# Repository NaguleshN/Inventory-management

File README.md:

# Inventory-management
The Inventory Management System will track and manage components inside iQube. It will include functionalities for managing product details, tracking stock levels, components taken out and returned back.
hello world.

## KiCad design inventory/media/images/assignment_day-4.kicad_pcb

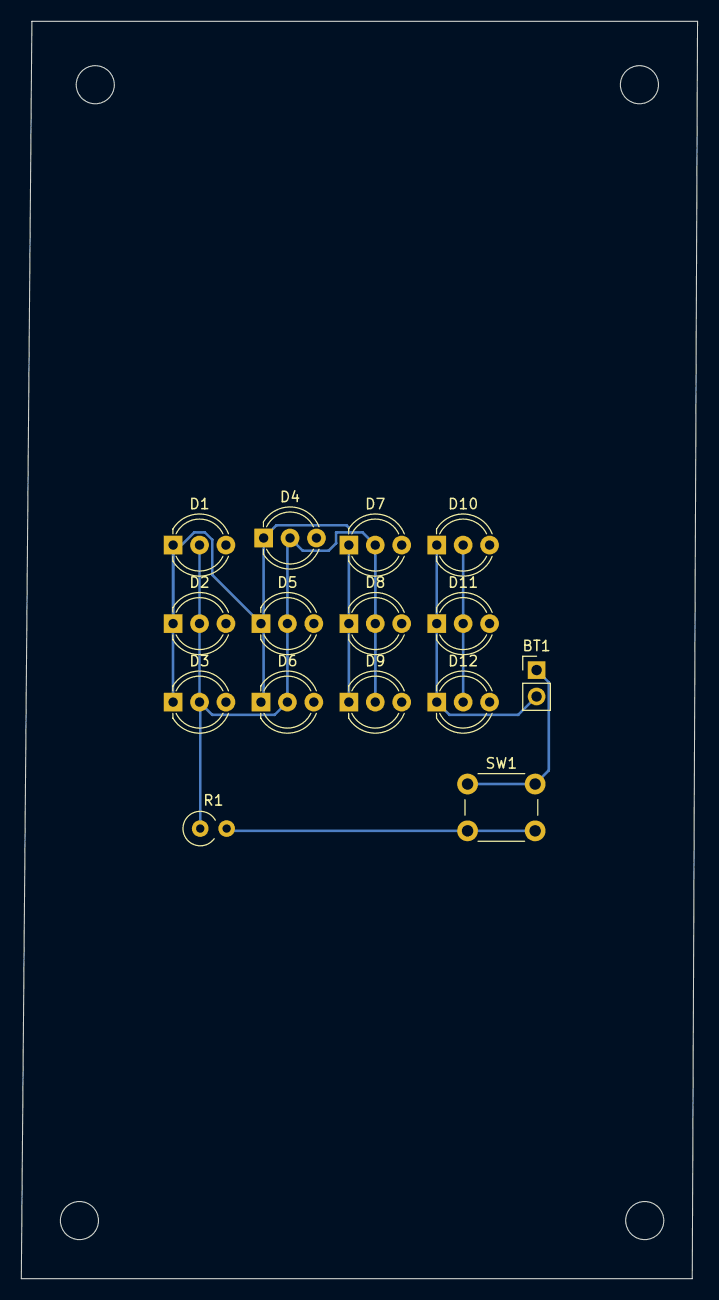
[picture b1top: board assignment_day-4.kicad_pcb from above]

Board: 2 copper layers, 65.0 x 120.9 mm, 15 parts (0 on the bottom side), 4 nets.

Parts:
BT1: Battery; PinHeader_1x02_P2.54mm_Vertical
D1, D2, D3, D4, D5, D6, D7, D8, D9, D10, D11, D12: LED; LED_D5.0mm-3
R1: R; R_Axial_DIN0309_L9.0mm_D3.2mm_P2.54mm_Vertical
SW1: SW_Push; SW_PUSH_6mm

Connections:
unnamed: BT1.1 (+), SW1.1
unnamed: BT1.2 (-), D1.1 (K), D2.1 (K), D3.1 (K), D4.1 (K), D5.1 (K), D6.1 (K), D7.1 (K), D8.1 (K), D9.1 (K), D10.1 (K), D11.1 (K), D12.1 (K)
unnamed: D1.2 (A), D2.2 (A), D3.2 (A), D4.2 (A), D5.2 (A), D6.2 (A), D7.2 (A), D8.2 (A), D9.2 (A), D10.2 (A), D11.2 (A), D12.2 (A), R1.1
unnamed: R1.2, SW1.2

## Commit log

2023-11-18 first change
2023-11-18 gitignore added
2023-11-18 start a project
2023-11-18 db created
2023-11-18 admin created
2023-11-18 db added
2023-11-18 Added foreign key
2023-11-18 category added
2023-11-18 choice added
2023-11-18 db successfully changed
2023-11-18 just Changes
2023-11-18 im chaai
2023-11-18 db delted
2023-11-19 base page added
2023-11-19 base page add
2023-11-19 home views
2023-11-19 Auto stash before merge of "main" and "origin/main"
    added product display
2023-11-19 add_product update
2023-11-19 query change
2023-11-19 about_page added
2023-11-19 Auto stash before merge of "main" and "origin/main"
    category page added
2023-11-19 Auto stash before merge of "main" and "origin/main"
    Wastage page added
2023-11-19 added view for category
2023-11-19 new feature
2023-11-19 Auto stash before merge of "main" and "origin/main"
    Wastage_page added with functionality
2023-11-19 gitignore
2023-11-19 pacth update
2023-11-19 added product description and cart btn
2023-11-19 added changes in cards and cart
2023-11-19 cart added
2023-11-19 patch2
2023-11-20 media
2023-11-20 media img add
2023-11-21 microsoft auth added
2023-11-22 cart function
2023-11-22 logout added
2023-11-23 final update
2023-11-25 25/11
2023-11-26 local try
2023-11-27 Log added
2023-11-30 models patch update 30/11
2023-11-30 microsoft auth update
2023-11-30 patch 2
2023-11-30 permission added
2023-11-30 updt
2023-12-01 '1_dec_review'
2023-12-02 editable quantity - 1
2023-12-06 usergroups-1
2023-12-06 usergroups-2
2023-12-08 img added
2023-12-08 No change1
2023-12-08 8th_dec
2023-12-08 Auto stash before merge of "main" and "origin/main"
2023-12-09 revert after cat
2023-12-09 No update1
2023-12-09 no change
2023-12-10 return form added
2023-12-10 UI added
2023-12-10 patch update 2.0
2023-12-10 small changes
2023-12-11 quantity count added
2023-12-11 11/12
2023-12-11 commits
2023-12-11 secret and microsoft auth
2023-12-11 change
2023-12-12 admin_list
2023-12-12 js functionality
2023-12-13 celery added
2023-12-13 js added
2023-12-14 Calender freeze
2023-12-19 pull the celery beat
2023-12-19 Revert "solved"
    This reverts commit 46ce384ae475cd0dca9fd1cd4a65216f001f253d, reversing
    changes made to c16d539e452ece3140e088d9a9bf76c80bc3c8a8.
2023-12-19 crud added
2023-12-19 Api integration
2023-12-22 docker create
2023-12-22 dockerfile added
2023-12-26 qty added
2023-12-26 env added
2023-12-26 dockerized
2023-12-27 err resolved
2023-12-29 truncate yml
2023-12-30 bug fix
2024-01-02 Cart bug fix
2024-01-06 cart bug2 fix
2024-01-06 added
2024-01-06 email added
2024-02-26 committed
2024-08-25 version,packageupdate
